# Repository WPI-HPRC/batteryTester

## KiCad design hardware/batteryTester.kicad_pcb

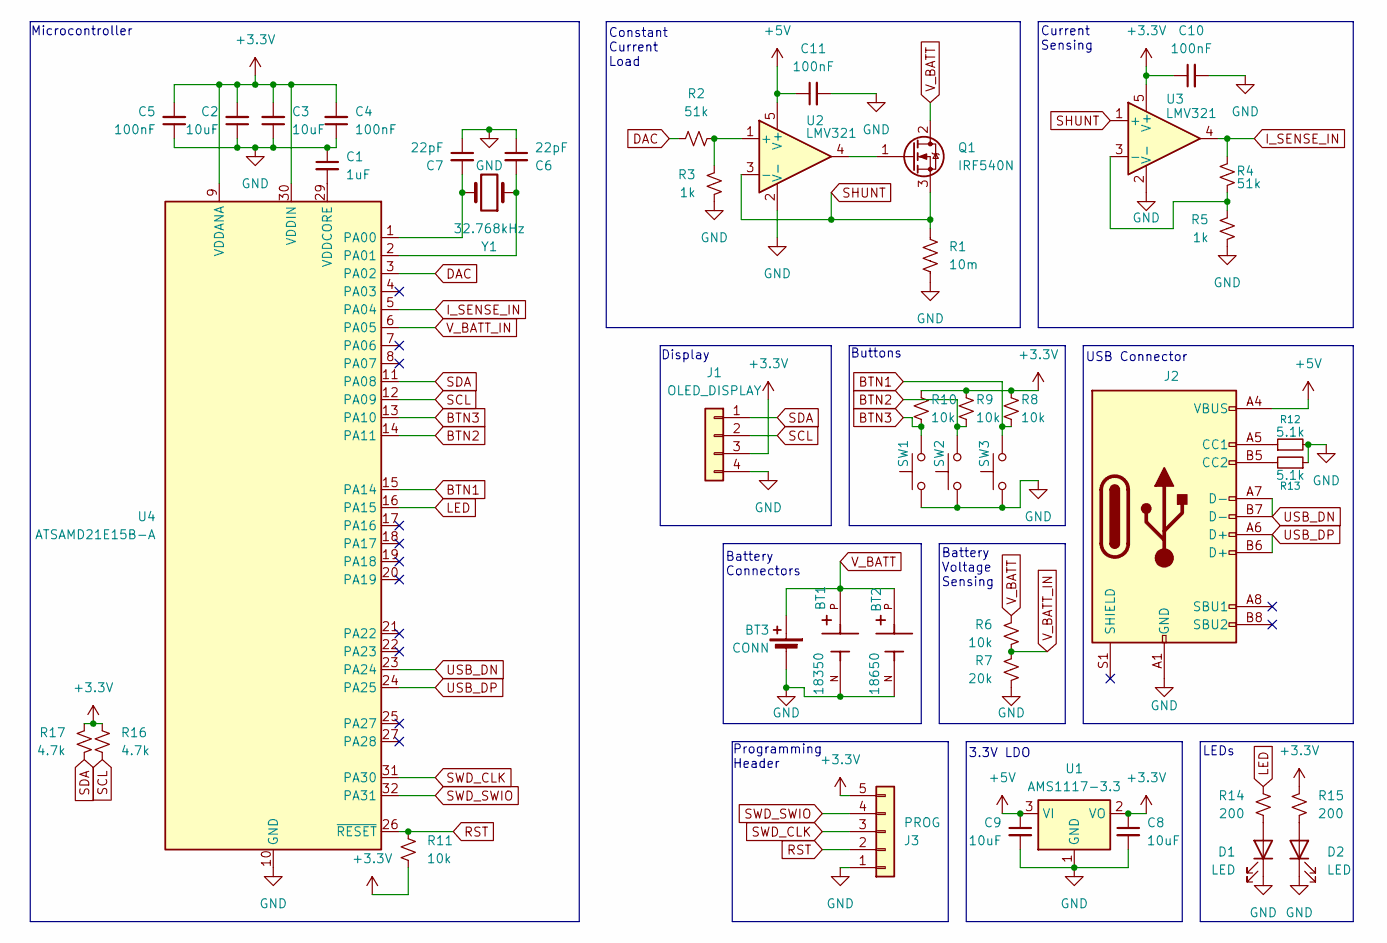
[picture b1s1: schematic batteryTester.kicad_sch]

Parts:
BT1: 18350; BAT_1095; PARTREV A
BT2: 18650; BAT_1043P; PARTREV D
BT3: CONN; PinHeader_1x02_P2.54mm_Vertical
C1: 1uF; C_0402_1005Metric
C2, C3, C8, C9: 10uF; C_0402_1005Metric
C4, C5, C10, C11: 100nF; C_0402_1005Metric
C6, C7: 22pF; C_0402_1005Metric
D1, D2: LED; LED_0603_1608Metric
J1: OLED_DISPLAY; PinSocket_1x04_P2.54mm_Vertical
J2: USB_C_Receptacle_USB2.0_16P; USB_C_Receptacle_GCT_USB4105-xx-A_16P_TopMnt_Horizontal
J3: PROG; PinHeader_1x05_P2.54mm_Vertical
Q1: IRF540N; TO-220-3_Vertical
R1: 10m; R_0805_2012Metric
R2, R4: 51k; R_0402_1005Metric
R3, R5: 1k; R_0402_1005Metric
R6, R8, R9, R10, R11: 10k; R_0402_1005Metric
R7: 20k; R_0402_1005Metric
R12, R13: 5.1k; R_0402_1005Metric
R14, R15: 200; R_0402_1005Metric
R16, R17: 4.7k; R_0402_1005Metric
SW1: START; SW_Push_1P1T_XKB_TS-1187A
SW2, SW3: STOP; SW_Push_1P1T_XKB_TS-1187A
U1: AMS1117-3.3; SOT-223-3_TabPin2
U2, U3: LMV321; SOT-23-5
U4: ATSAMD21E15B-A; TQFP-32_7x7mm_P0.8mm
Y1: 32.768kHz; Crystal_SMD_3215-2Pin_3.2x1.5mm

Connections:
+3.3V: C2.2, C3.2, C4.2, C5.2, C8.1, C10.1, J1.3, J3.5, R8.1, R9.1, R10.1, R11.1, R15.1, R16.1, R17.1, U1.2 (VO), U3.5 (V+), U4.9 (VDDANA), U4.30 (VDDIN); also elsewhere on the board
+5V: C9.1, C11.1, J2.A4 (VBUS), J2.A9 (VBUS), J2.B4 (VBUS), J2.B9 (VBUS), U1.3 (VI), U2.5 (V+)
BTN1: R8.2, SW3.2, U4.15 (PA14)
BTN2: R9.2, SW2.2, U4.14 (PA11)
BTN3: R10.2, SW1.2, U4.13 (PA10)
DAC: R2.1, U4.3 (PA02)
GND: BT1.N, BT2.N, BT3.2 (-), C1.1, C2.1, C3.1, C4.1, C5.1, C6.1, C7.1, C8.2, C9.2, C10.2, C11.2, D1.1 (K), D2.1 (K), J1.4, J2.A1 (GND), J2.A12 (GND), J2.B1 (GND), J2.B12 (GND), J3.1, R1.2, R3.1, R5.2, R7.2, R12.2, R13.1, SW1.1, SW2.1, SW3.1, U1.1 (GND), U2.2 (V-), U3.2 (V-), U4.10 (GND), U4.28 (GND); also elsewhere on the board
I_SENSE_IN: R4.2, U3.4, U4.5 (PA04)
LED: R14.1, U4.16 (PA15)
unnamed: D1.2 (A), R14.2
unnamed: D2.2 (A), R15.2
unnamed: J2.A5 (CC1), R12.1
unnamed: J2.B5 (CC2), R13.2
unnamed: Q1.1 (G), U2.4
unnamed: R2.2, R3.2, U2.1 (+)
unnamed: R4.1, R5.1, U3.3 (-)
unnamed: C7.2, U4.1 (PA00), Y1.2
unnamed: C6.2, U4.2 (PA01), Y1.1
unnamed: C1.2, U4.29 (VDDCORE)
RST: J3.2, R11.2, U4.26 (~RESET)
SCL: J1.2, R16.2, U4.12 (PA09); also elsewhere on the board
SDA: J1.1, R17.2, U4.11 (PA08); also elsewhere on the board
SHUNT: Q1.3 (S), R1.1, U2.3 (-), U3.1 (+)
SWD_CLK: J3.3, U4.31 (PA30)
SWD_SWIO: J3.4, U4.32 (PA31)
USB_DN: J2.A7 (D-), J2.B7 (D-), U4.23 (PA24)
USB_DP: J2.A6 (D+), J2.B6 (D+), U4.24 (PA25)
V_BATT: BT1.P, BT2.P, BT3.1 (+), Q1.2 (D), R6.1
V_BATT_IN: R6.2, R7.1, U4.6 (PA05)

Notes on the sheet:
Battery Connectors
Programming Header
Battery Voltage Sensing
Microcontroller
Display
LEDs
USB Connector
3.3V LDO
Current Sensing
Buttons
Constant Current Load

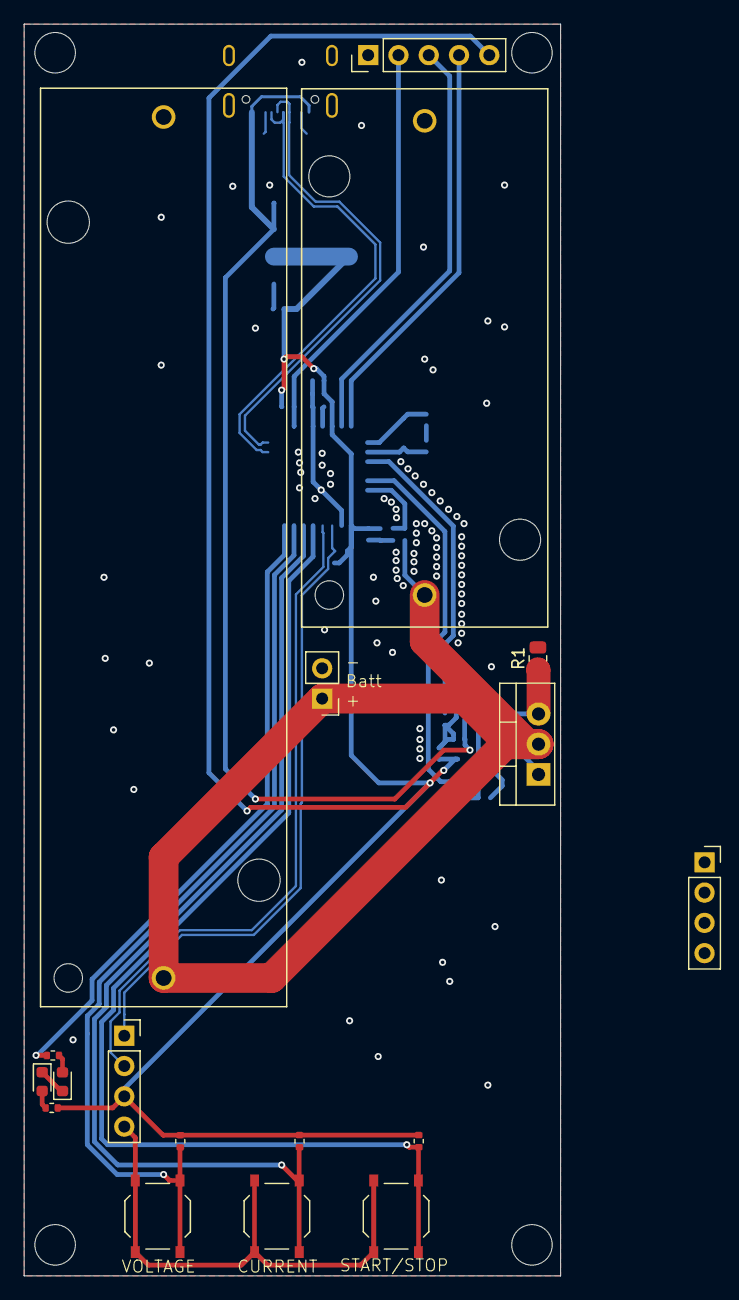
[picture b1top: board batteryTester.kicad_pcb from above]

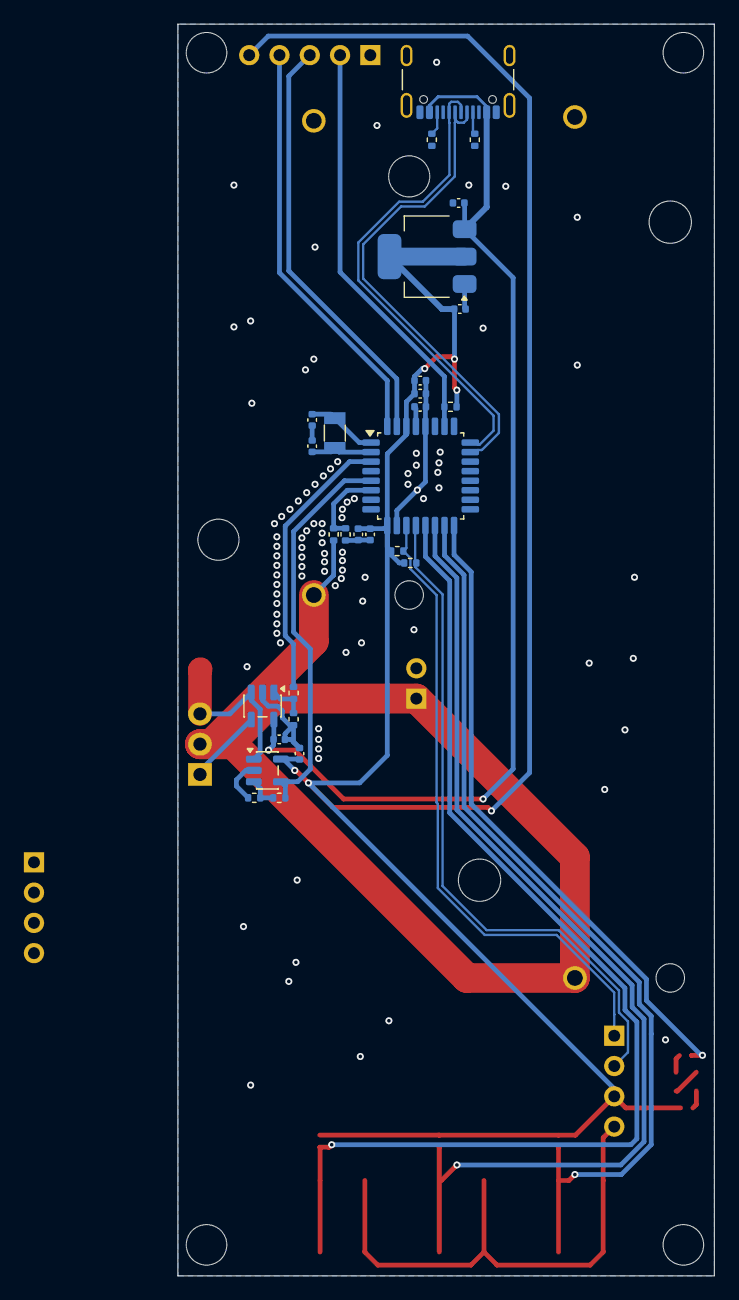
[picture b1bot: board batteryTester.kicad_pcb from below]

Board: 2 copper layers, 45.0 x 105.0 mm, 46 parts (28 on the bottom side), 29 nets.

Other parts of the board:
J1#2: OLED_DISPLAY; PinSocket_1x04_P2.54mm_Vertical

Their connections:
+3.3V: J1#2.3; also elsewhere on the board
GND: J1#2.4; also elsewhere on the board
SCL: J1#2.2; also elsewhere on the board
SDA: J1#2.1; also elsewhere on the board

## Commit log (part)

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2026-03-17 works?
2026-03-19 add gitignore
2026-03-19 add i2c pullups
2026-04-06 re-org for code
2026-04-13 ordering new uC
2026-04-27 fix folders
